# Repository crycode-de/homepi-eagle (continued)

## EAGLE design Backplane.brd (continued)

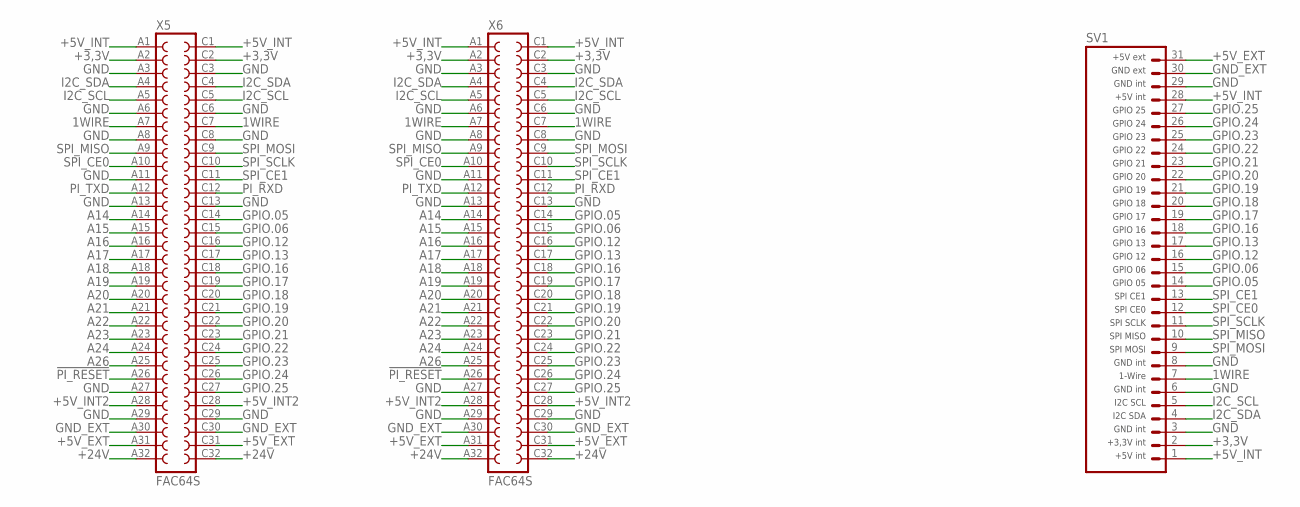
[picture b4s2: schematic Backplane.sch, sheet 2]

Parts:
SV1: PLATINENVERBINDER-31SMD-BOTTOM; PLATINENVERBINDER-31-SMD_BOTTOM
X5, X6: FAC64S

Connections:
1WIRE: SV1.7, X5.A7, X5.C7, X6.A7, X6.C7; also elsewhere on the board
!PI_RESET: X5.A26, X6.A26; also elsewhere on the board
+3,3V: SV1.2, X5.A2, X5.C2, X6.A2, X6.C2; also elsewhere on the board
+5V_EXT: SV1.31, X5.A31, X5.C31, X6.A31, X6.C31; also elsewhere on the board
+5V_INT: SV1.1, SV1.28, X5.A1, X5.C1, X6.A1, X6.C1; also elsewhere on the board
+5V_INT2: X5.A28, X5.C28, X6.A28, X6.C28; also elsewhere on the board
+24V: X5.A32, X5.C32, X6.A32, X6.C32; also elsewhere on the board
A14: X5.A14, X6.A14; also elsewhere on the board
A15: X5.A15, X6.A15; also elsewhere on the board
A16: X5.A16, X6.A16; also elsewhere on the board
A17: X5.A17, X6.A17; also elsewhere on the board
A18: X5.A18, X6.A18; also elsewhere on the board
A19: X5.A19, X6.A19; also elsewhere on the board
A20: X5.A20, X6.A20; also elsewhere on the board
A21: X5.A21, X6.A21; also elsewhere on the board
A22: X5.A22, X6.A22; also elsewhere on the board
A23: X5.A23, X6.A23; also elsewhere on the board
A24: X5.A24, X6.A24; also elsewhere on the board
A26: X5.A25, X6.A25; also elsewhere on the board
GND: SV1.3, SV1.6, SV1.8, SV1.29, X5.A3, X5.A6, X5.A8, X5.A11, X5.A13, X5.A27, X5.A29, X5.C3, X5.C6, X5.C8, X5.C13, X5.C29, X6.A3, X6.A6, X6.A8, X6.A11, X6.A13, X6.A27, X6.A29, X6.C3, X6.C6, X6.C8, X6.C13, X6.C29; also elsewhere on the board
GND_EXT: SV1.30, X5.A30, X5.C30, X6.A30, X6.C30; also elsewhere on the board
GPIO.05: SV1.14, X5.C14, X6.C14; also elsewhere on the board
GPIO.06: SV1.15, X5.C15, X6.C15; also elsewhere on the board
GPIO.12: SV1.16, X5.C16, X6.C16; also elsewhere on the board
GPIO.13: SV1.17, X5.C17, X6.C17; also elsewhere on the board
GPIO.16: SV1.18, X5.C18, X6.C18; also elsewhere on the board
GPIO.17: SV1.19, X5.C19, X6.C19; also elsewhere on the board
GPIO.18: SV1.20, X5.C20, X6.C20; also elsewhere on the board
GPIO.19: SV1.21, X5.C21, X6.C21; also elsewhere on the board
GPIO.20: SV1.22, X5.C22, X6.C22; also elsewhere on the board
GPIO.21: SV1.23, X5.C23, X6.C23; also elsewhere on the board
GPIO.22: SV1.24, X5.C24, X6.C24; also elsewhere on the board
GPIO.23: SV1.25, X5.C25, X6.C25; also elsewhere on the board
GPIO.24: SV1.26, X5.C26, X6.C26; also elsewhere on the board
GPIO.25: SV1.27, X5.C27, X6.C27; also elsewhere on the board
I2C_SCL: SV1.5, X5.A5, X5.C5, X6.A5, X6.C5; also elsewhere on the board
I2C_SDA: SV1.4, X5.A4, X5.C4, X6.A4, X6.C4; also elsewhere on the board
PI_RXD: X5.C12, X6.C12; also elsewhere on the board
PI_TXD: X5.A12, X6.A12; also elsewhere on the board
SPI_CE0: SV1.12, X5.A10, X6.A10; also elsewhere on the board
SPI_CE1: SV1.13, X5.C11, X6.C11; also elsewhere on the board
SPI_MISO: SV1.10, X5.A9, X6.A9; also elsewhere on the board
SPI_MOSI: SV1.9, X5.C9, X6.C9; also elsewhere on the board
SPI_SCLK: SV1.11, X5.C10, X6.C10; also elsewhere on the board

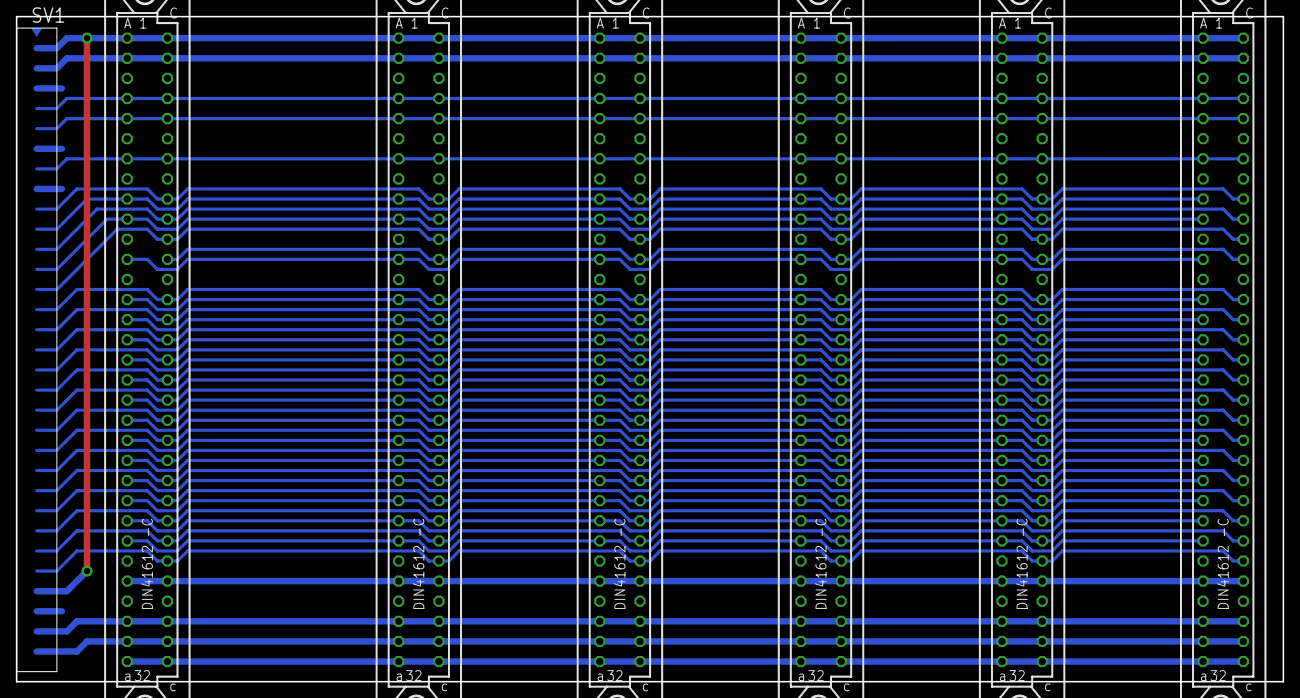
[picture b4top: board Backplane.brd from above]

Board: 2 copper layers, 160.0 x 84.0 mm, 7 parts (0 on the bottom side), 44 nets.

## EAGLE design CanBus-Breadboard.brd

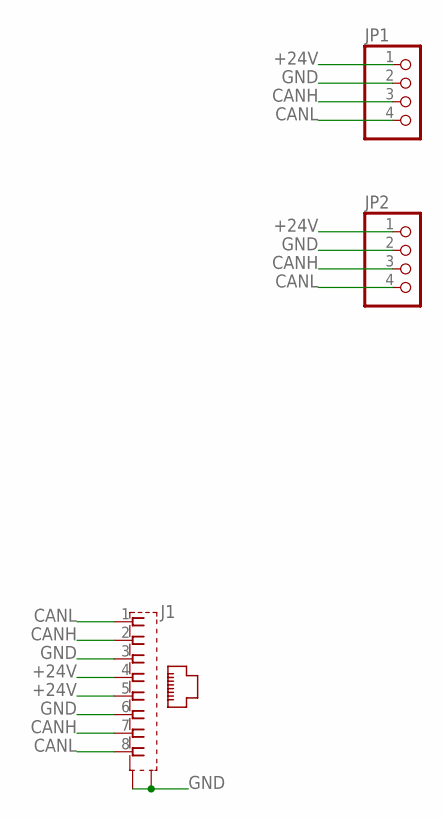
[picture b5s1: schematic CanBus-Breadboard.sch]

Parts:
J1: 555141-1; MEBP_8-8G
JP1, JP2: PINHD-1X4; 1X04

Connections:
+24V: J1.4, J1.5, JP1.1, JP2.1
CANH: J1.2, J1.7, JP1.3, JP2.3
CANL: J1.1, J1.8, JP1.4, JP2.4
GND: J1.3, J1.6, J1.G1 (S1), J1.G2 (S2), JP1.2, JP2.2

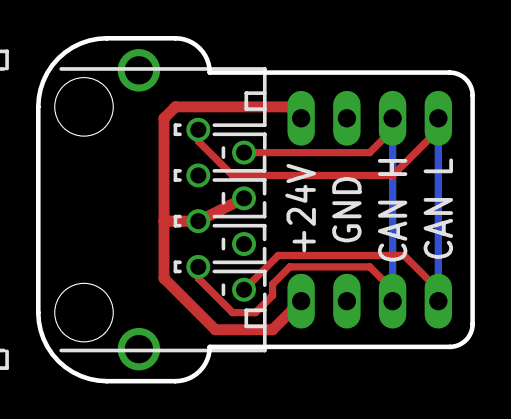
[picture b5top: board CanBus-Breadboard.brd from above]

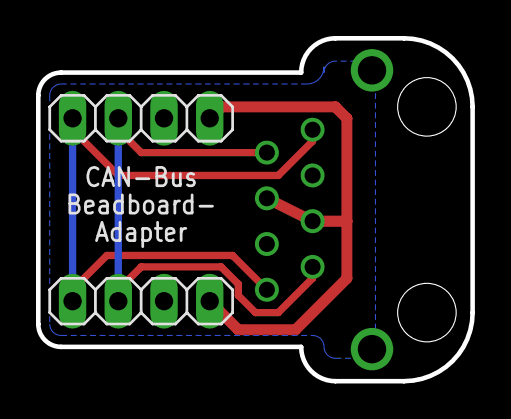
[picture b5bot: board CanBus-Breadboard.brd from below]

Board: 2 copper layers, 24.1 x 19.1 mm, 3 parts (2 on the bottom side), 4 nets.

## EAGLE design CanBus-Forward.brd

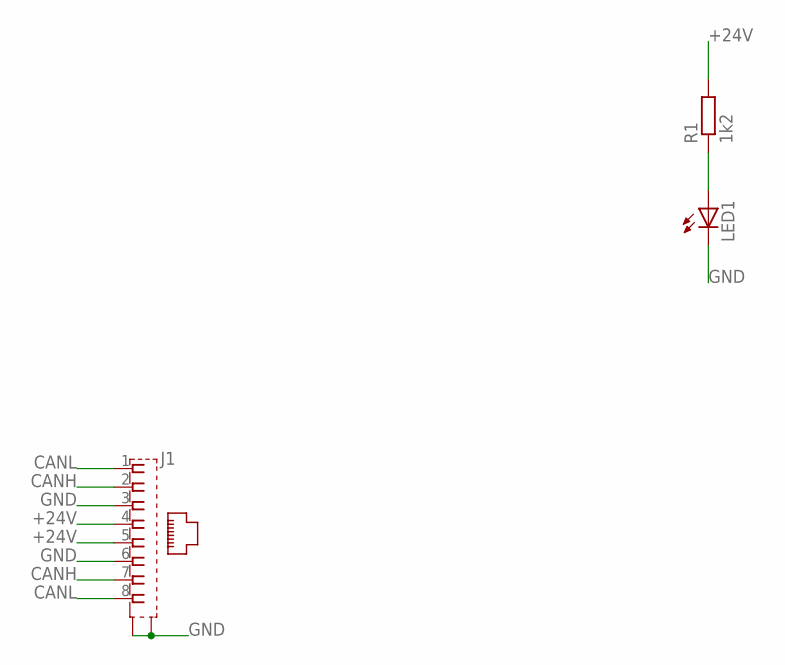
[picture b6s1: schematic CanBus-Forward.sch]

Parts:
J1: 555141-1; MEBP_8-8G
LED1: LEDCHIPLED_1206; CHIPLED_1206
R1: 1k2; R1206

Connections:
+24V: J1.4, J1.5, R1.2
CANH: J1.2, J1.7
CANL: J1.1, J1.8
GND: J1.3, J1.6, J1.G1 (S1), J1.G2 (S2), LED1.C
unnamed: LED1.A, R1.1

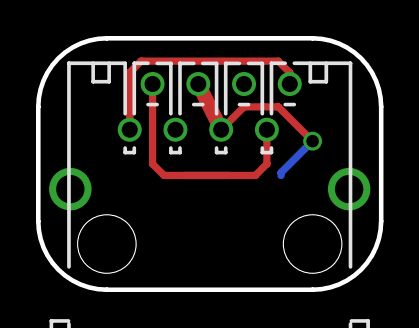
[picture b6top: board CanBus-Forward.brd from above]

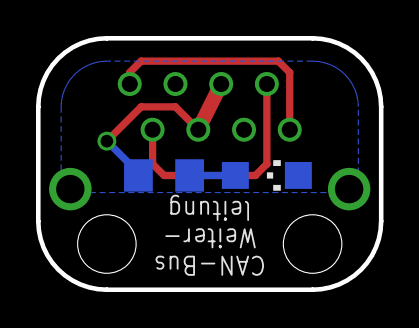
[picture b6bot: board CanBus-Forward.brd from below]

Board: 2 copper layers, 19.1 x 14.0 mm, 3 parts (2 on the bottom side), 5 nets.

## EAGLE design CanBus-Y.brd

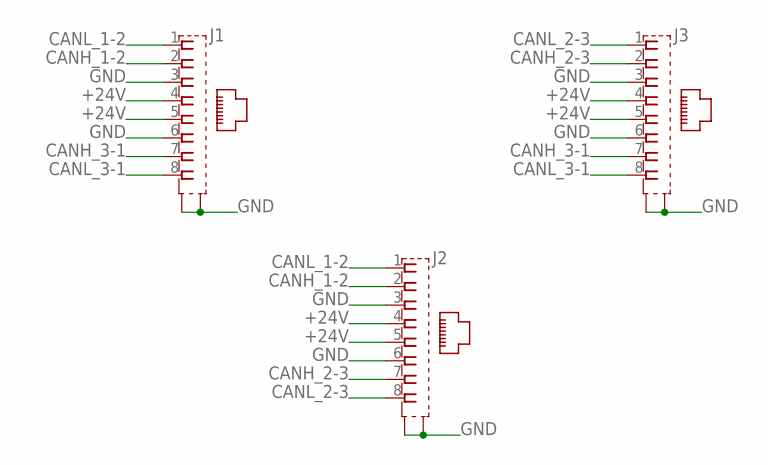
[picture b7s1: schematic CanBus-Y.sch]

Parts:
J1, J2, J3: 555141-1; MEBP_8-8G

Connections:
+24V: J1.4, J1.5, J2.4, J2.5, J3.4, J3.5
CANH_1-2: J1.2, J2.2
CANH_2-3: J2.7, J3.2
CANH_3-1: J1.7, J3.7
CANL_1-2: J1.1, J2.1
CANL_2-3: J2.8, J3.1
CANL_3-1: J1.8, J3.8
GND: J1.3, J1.6, J1.G1 (S1), J1.G2 (S2), J2.3, J2.6, J2.G1 (S1), J2.G2 (S2), J3.3, J3.6, J3.G1 (S1), J3.G2 (S2)

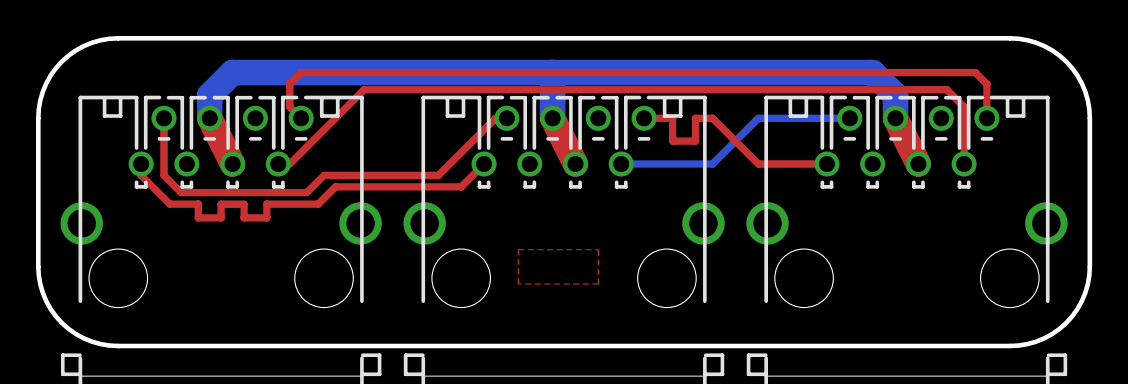
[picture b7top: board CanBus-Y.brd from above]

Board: 2 copper layers, 58.4 x 17.1 mm, 3 parts (0 on the bottom side), 8 nets.

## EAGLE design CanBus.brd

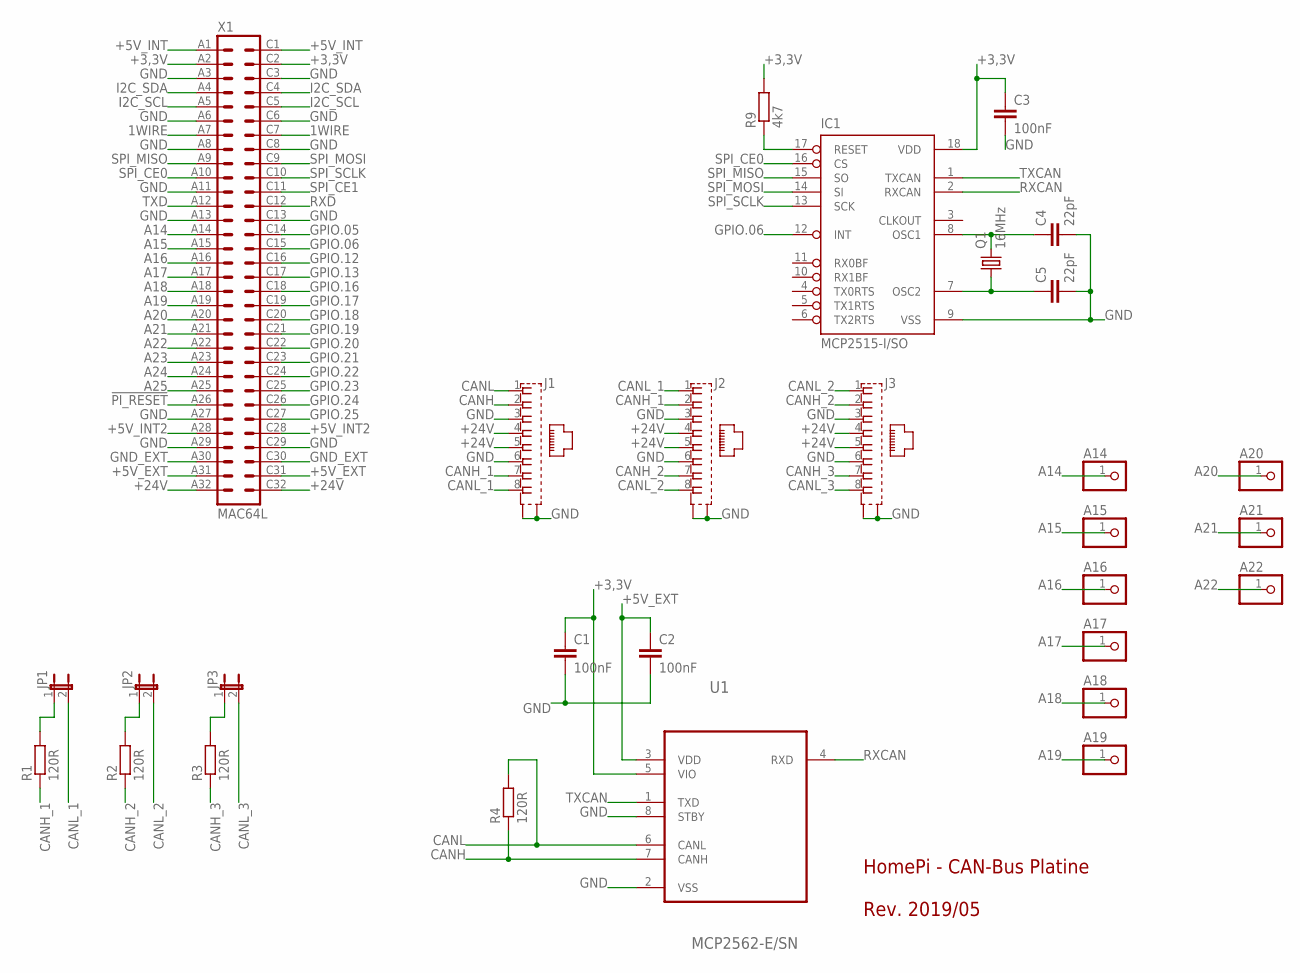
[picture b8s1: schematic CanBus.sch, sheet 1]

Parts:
A14, A15, A16, A17, A18, A19, A20, A21, A22: PINHD-1X1; 1X01
C1, C2, C3: 100nF; C1206
C4, C5: 22pF; C1206
IC1: MCP2515-I/SO; SO18L
J1, J2, J3: 555141-1; MEBP_8-8G
JP1, JP2, JP3: JP1E; JP1
Q1: 16MHz; HC49UP
R1, R2, R3, R4: 120R; R1206
R9: 4k7; R1206
U1: MCP2562-E/SN; SO08
X1: MAC64L

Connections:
1WIRE: X1.A7, X1.C7
!PI_RESET: X1.A26; also elsewhere on the board
+3,3V: C1.1, C3.1, IC1.18 (VDD), R9.2, U1.5 (VIO), X1.A2, X1.C2; also elsewhere on the board
+5V_EXT: C2.1, U1.3 (VDD), X1.A31, X1.C31; also elsewhere on the board
+5V_INT: X1.A1, X1.C1
+5V_INT2: X1.A28, X1.C28
+24V: J1.4, J1.5, J2.4, J2.5, J3.4, J3.5, X1.A32, X1.C32
A14: A14.1, X1.A14
A15: A15.1, X1.A15
A16: A16.1, X1.A16
A17: A17.1, X1.A17
A18: A18.1, X1.A18
A19: A19.1, X1.A19
A20: A20.1, X1.A20
A21: A21.1, X1.A21
A22: A22.1, X1.A22
A23: X1.A23
A24: X1.A24
A25: X1.A25
CANH: J1.2, R4.1, U1.7 (CANH); also elsewhere on the board
CANH_1: J1.7, J2.2, R1.1
CANH_2: J2.7, J3.2, R2.1
CANH_3: J3.7, R3.1
CANL: J1.1, R4.2, U1.6 (CANL); also elsewhere on the board
CANL_1: J1.8, J2.1, JP1.2
CANL_2: J2.8, J3.1, JP2.2
CANL_3: J3.8, JP3.2
GND: C1.2, C2.2, C3.2, C4.2, C5.2, IC1.9 (VSS), J1.3, J1.6, J1.G1 (S1), J1.G2 (S2), J2.3, J2.6, J2.G1 (S1), J2.G2 (S2), J3.3, J3.6, J3.G1 (S1), J3.G2 (S2), U1.2 (VSS), U1.8 (STBY), X1.A3, X1.A6, X1.A8, X1.A11, X1.A13, X1.A27, X1.A29, X1.C3, X1.C6, X1.C8, X1.C13, X1.C29; also elsewhere on the board
GND_EXT: X1.A30, X1.C30
GPIO.05: X1.C14
GPIO.06: IC1.12 (INT), X1.C15
GPIO.12: X1.C16
GPIO.13: X1.C17
GPIO.16: X1.C18
GPIO.17: X1.C19
GPIO.18: X1.C20
GPIO.19: X1.C21
GPIO.20: X1.C22
GPIO.21: X1.C23
GPIO.22: X1.C24
GPIO.23: X1.C25
GPIO.24: X1.C26
GPIO.25: X1.C27
I2C_SCL: X1.A5, X1.C5
I2C_SDA: X1.A4, X1.C4
unnamed: C4.1, IC1.8 (OSC1), Q1.2
unnamed: IC1.17 (RESET), R9.1
unnamed: JP2.1, R2.2
unnamed: C5.1, IC1.7 (OSC2), Q1.1
unnamed: JP1.1, R1.2
unnamed: JP3.1, R3.2
RXCAN: IC1.2 (RXCAN), U1.4 (RXD)
RXD: X1.C12
SPI_CE0: IC1.16 (CS), X1.A10
SPI_CE1: X1.C11
SPI_MISO: IC1.15 (SO), X1.A9
SPI_MOSI: IC1.14 (SI), X1.C9
SPI_SCLK: IC1.13 (SCK), X1.C10
TXCAN: IC1.1 (TXCAN), U1.1 (TXD)
TXD: X1.A12

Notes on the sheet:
HomePi - CAN-Bus Platine Rev. 2019/05

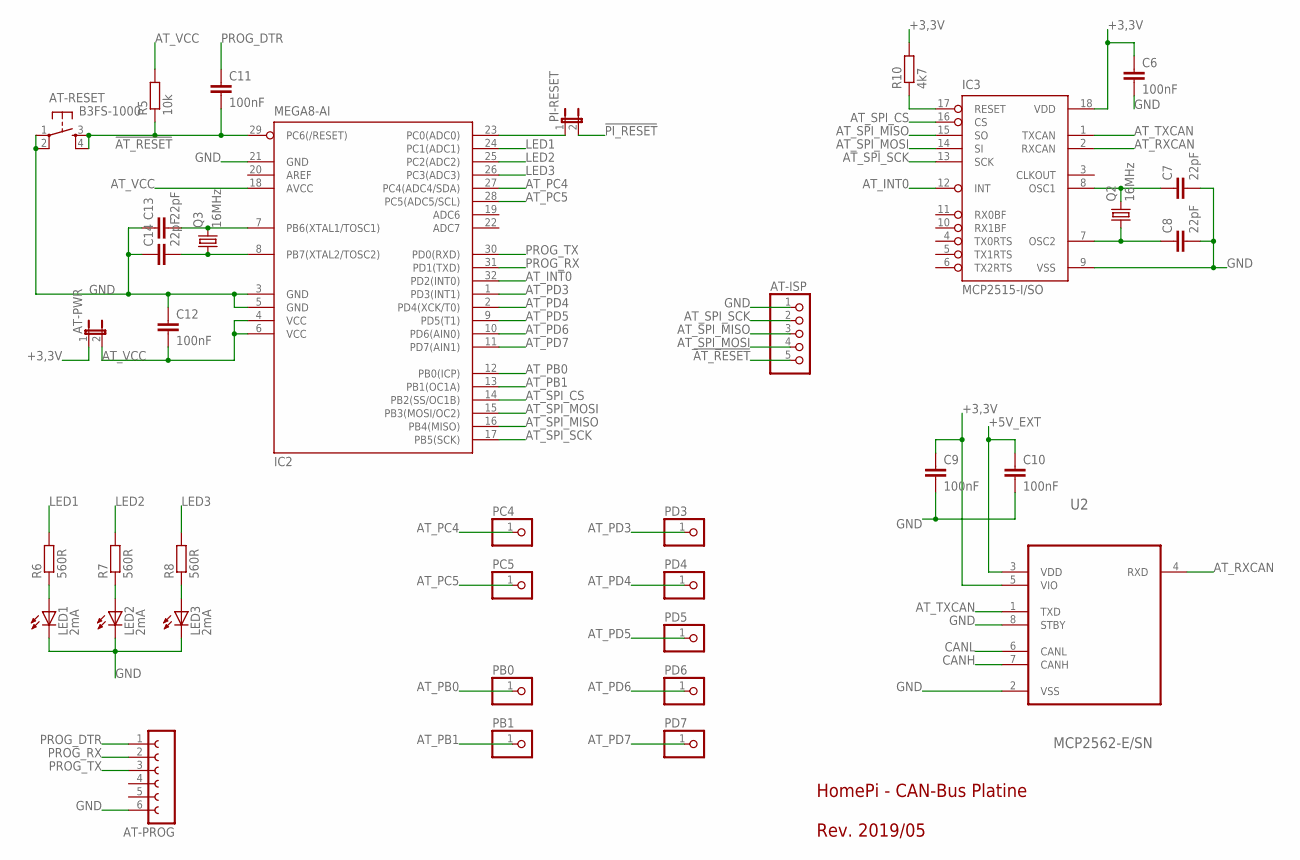
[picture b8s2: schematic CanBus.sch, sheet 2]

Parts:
AT-ISP: PINHD-1X5; 1X05
AT-PROG: FE06W
AT-PWR: JP1E; JP1
AT-RESET: B3FS-1000
C6, C9, C10, C11, C12: 100nF; C1206
C7, C8, C13, C14: 22pF; C1206
IC2: MEGA8-AI; TQFP32-08
IC3: MCP2515-I/SO; SO18L
LED1, LED2, LED3: 2mA; LED3MM
PB0, PB1: PINHD-1X1; 1X01
PC4, PC5: PINHD-1X1; 1X01
PD3, PD4, PD5, PD6, PD7: PINHD-1X1; 1X01
PI-RESET: JP1E; JP1
Q2, Q3: 16MHz; HC49UP
R5: 10k; R1206
R6, R7, R8: 560R; R1206
R10: 4k7; R1206
U2: MCP2562-E/SN; SO08

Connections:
!AT_RESET: AT-ISP.5, AT-RESET.3 (S), AT-RESET.4 (S1), C11.2, IC2.29 (PC6(/RESET)), R5.1
!PI_RESET: PI-RESET.2; also elsewhere on the board
+3,3V: AT-PWR.1, C6.1, C9.1, IC3.18 (VDD), R10.2, U2.5 (VIO); also elsewhere on the board
+5V_EXT: C10.1, U2.3 (VDD); also elsewhere on the board
AT_INT0: IC2.32 (PD2(INT0)), IC3.12 (INT)
AT_PB0: IC2.12 (PB0(ICP)), PB0.1
AT_PB1: IC2.13 (PB1(OC1A)), PB1.1
AT_PC4: IC2.27 (PC4(ADC4/SDA)), PC4.1
AT_PC5: IC2.28 (PC5(ADC5/SCL)), PC5.1
AT_PD3: IC2.1 (PD3(INT1)), PD3.1
AT_PD4: IC2.2 (PD4(XCK/T0)), PD4.1
AT_PD5: IC2.9 (PD5(T1)), PD5.1
AT_PD6: IC2.10 (PD6(AIN0)), PD6.1
AT_PD7: IC2.11 (PD7(AIN1)), PD7.1
AT_RXCAN: IC3.2 (RXCAN), U2.4 (RXD)
AT_SPI_CS: IC2.14 (PB2(SS/OC1B)), IC3.16 (CS)
AT_SPI_MISO: AT-ISP.3, IC2.16 (PB4(MISO)), IC3.15 (SO)
AT_SPI_MOSI: AT-ISP.4, IC2.15 (PB3(MOSI/OC2)), IC3.14 (SI)
AT_SPI_SCK: AT-ISP.2, IC2.17 (PB5(SCK)), IC3.13 (SCK)
AT_TXCAN: IC3.1 (TXCAN), U2.1 (TXD)
AT_VCC: AT-PWR.2, C12.2, IC2.4 (VCC), IC2.6 (VCC), IC2.18 (AVCC), R5.2
CANH: U2.7 (CANH); also elsewhere on the board
CANL: U2.6 (CANL); also elsewhere on the board
GND: AT-ISP.1, AT-PROG.6, AT-RESET.1, AT-RESET.2 (P1), C6.2, C7.2, C8.2, C9.2, C10.2, C12.1, C13.1, C14.1, IC2.3 (GND), IC2.5 (GND), IC2.21 (GND), IC3.9 (VSS), LED1.K (C), LED2.K (C), LED3.K (C), U2.2 (VSS), U2.8 (STBY); also elsewhere on the board
LED1: IC2.24 (PC1(ADC1)), R6.2
LED2: IC2.25 (PC2(ADC2)), R7.2
LED3: IC2.26 (PC3(ADC3)), R8.2
unnamed: IC3.17 (RESET), R10.1
unnamed: C7.1, IC3.8 (OSC1), Q2.2
unnamed: C8.1, IC3.7 (OSC2), Q2.1
unnamed: IC2.23 (PC0(ADC0)), PI-RESET.1
unnamed: C13.2, IC2.7 (PB6(XTAL1/TOSC1)), Q3.2
unnamed: C14.2, IC2.8 (PB7(XTAL2/TOSC2)), Q3.1
unnamed: LED1.A, R6.1
unnamed: LED2.A, R7.1
unnamed: LED3.A, R8.1
PROG_DTR: AT-PROG.1, C11.1
PROG_RX: AT-PROG.2, IC2.31 (PD1(TXD))
PROG_TX: AT-PROG.3, IC2.30 (PD0(RXD))

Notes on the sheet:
HomePi - CAN-Bus Platine Rev. 2019/05

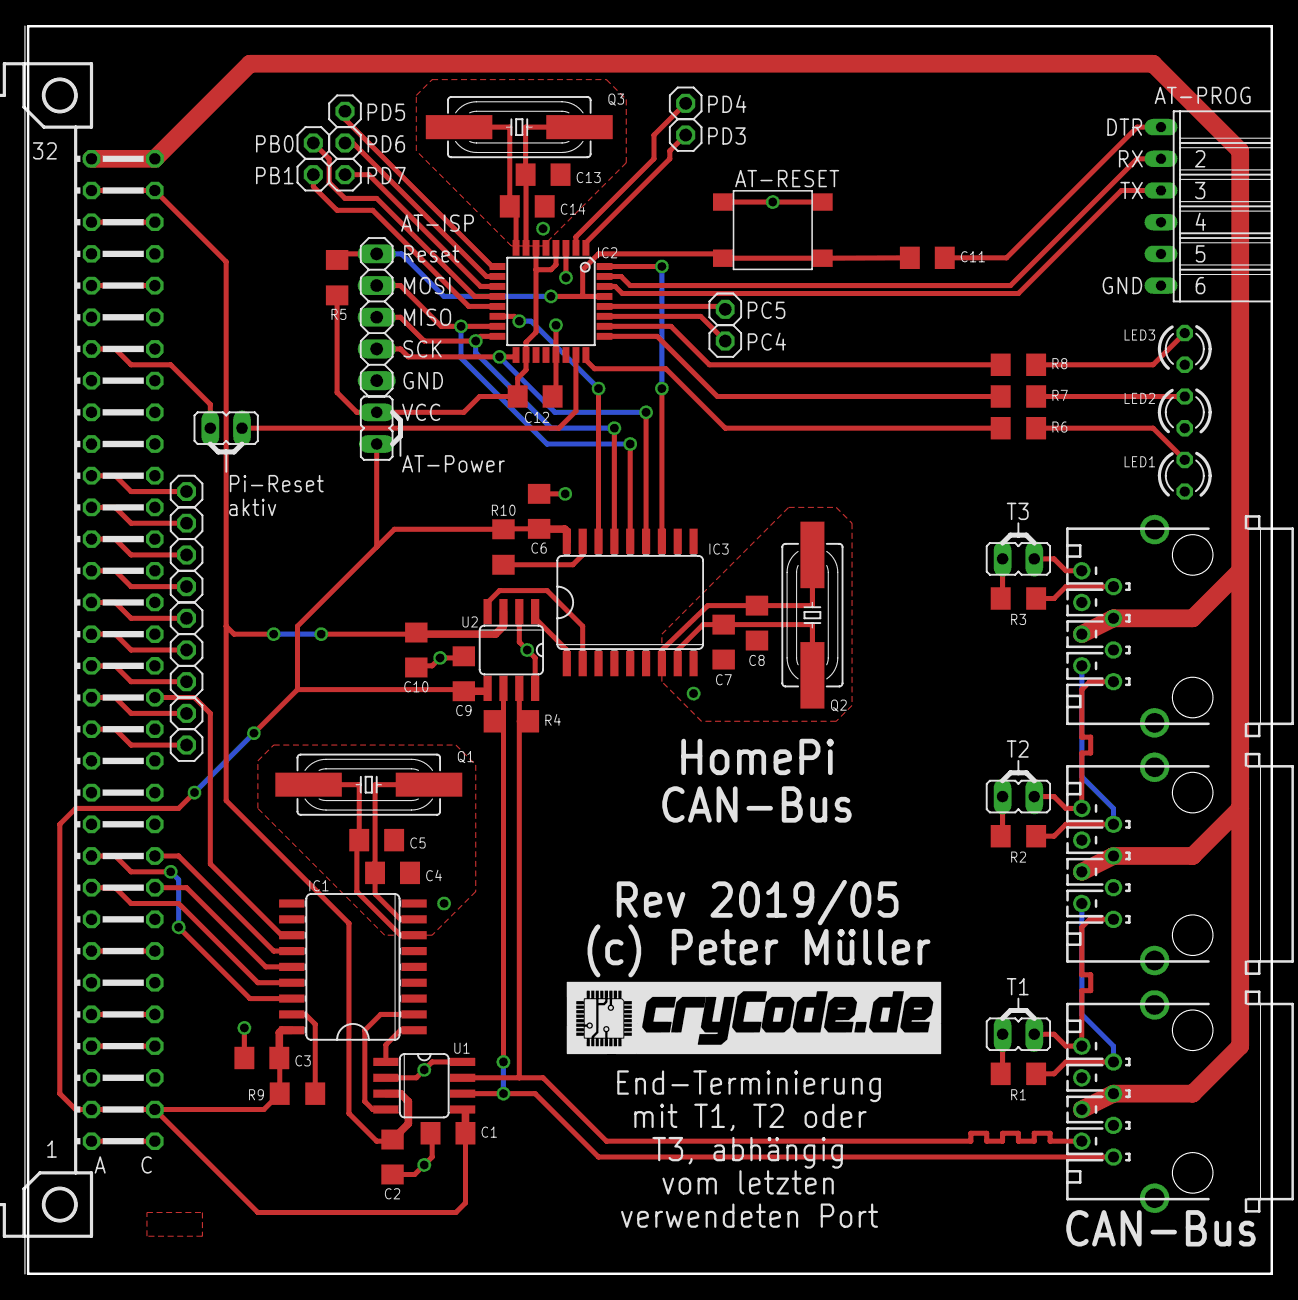
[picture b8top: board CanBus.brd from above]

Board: 2 copper layers, 99.7 x 100.0 mm, 66 parts (0 on the bottom side), 74 nets.

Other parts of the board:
U$1: 30MM
